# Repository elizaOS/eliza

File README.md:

# Eliza on Vibestack

This workspace specifies the replacement for `@elizaos/core` on Vibestack.
The specification covers requirements, Quint models, and the generated
contracts for a future VibeLang and Effect implementation.

Start with [the Grace and AlphaPhone contracts](spec/downstream/index.md),
[the core specification](spec/core/index.md),
[the agent procedure](AGENTS.md) and [the spec reference](SPEC.md).
The source baseline is Eliza commit
`72fed7e4069ecd35d61d886ab6eec5c02c137517`. The orphan `vibestack` branch
starts from elizaOS/eliza-vibestack commit
`71d7b30f404b91d7ec48741ac288d6c8d911f3e2`.

## Setup and verification

Use Node 26, pnpm 10.24.0 and Dafny 4.11.

```sh
pnpm install --frozen-lockfile
pnpm gen
pnpm check
pnpm verify
```

`pnpm check` generates the contracts, checks model traces and replay,
proves safety obligations, runs available journeys, and lists changes for
review. `pnpm accept` records the user's review. The imported application
in `apps/app` exercises the toolchain. Core implementation and npm
consumer acceptance are separate later work.

[The Vibestack toolchain guide](vibestack/README.md) explains Studio,
commands, examples and generated files. [Contributing](CONTRIBUTING.md)
describes the repository checks. The MIT license is in [LICENSE](LICENSE).

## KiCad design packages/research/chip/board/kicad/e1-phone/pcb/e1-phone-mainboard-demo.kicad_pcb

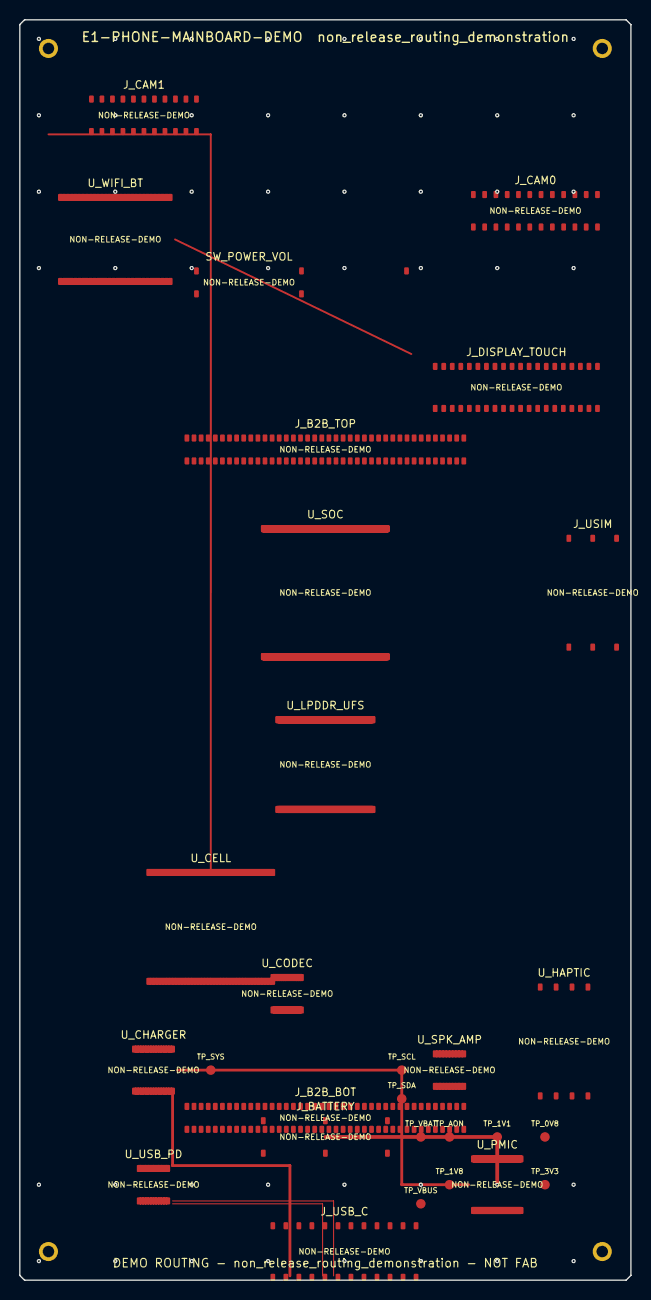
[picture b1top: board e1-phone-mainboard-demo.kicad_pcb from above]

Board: 10 copper layers, 64.0 x 132.0 mm, 29 parts (0 on the bottom side), 40 nets.

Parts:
J_B2B_BOT: DEMO; J_B2B_BOT
J_B2B_TOP: DEMO; J_B2B_TOP
J_BATTERY: DEMO; J_BATTERY
J_CAM0: DEMO; J_CAM0
J_CAM1: DEMO; J_CAM1
J_DISPLAY_TOUCH: DEMO; J_DISPLAY_TOUCH
J_USB_C: DEMO; J_USB_C
J_USIM: DEMO; J_USIM
SW_POWER_VOL: DEMO; SW_POWER_VOL
TP_0V8: +0V8; TP_0V8
TP_1V1: +1V1; TP_1V1
TP_1V8: +1V8; TP_1V8
TP_3V3: +3V3; TP_3V3
TP_AON: AON_1V8; TP_AON
TP_SCL: I2C0_SCL; TP_SCL
TP_SDA: I2C0_SDA; TP_SDA
TP_SYS: SYS; TP_SYS
TP_VBAT: VBAT; TP_VBAT
TP_VBUS: VBUS; TP_VBUS
U_CELL: DEMO; U_CELL
U_CHARGER: DEMO; U_CHARGER
U_CODEC: DEMO; U_CODEC
U_HAPTIC: DEMO; U_HAPTIC
U_LPDDR_UFS: DEMO; U_LPDDR_UFS
U_PMIC: DEMO; U_PMIC
U_SOC: DEMO; U_SOC
U_SPK_AMP: DEMO; U_SPK_AMP
U_USB_PD: DEMO; U_USB_PD
U_WIFI_BT: DEMO; U_WIFI_BT

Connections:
+0V8: TP_0V8.1, U_PMIC.7, U_PMIC.16, U_PMIC.25, U_PMIC.34, U_PMIC.43, U_PMIC.52, U_PMIC.61, U_SOC.1, U_SOC.9, U_SOC.17, U_SOC.25, U_SOC.33, U_SOC.41, U_SOC.49, U_SOC.57, U_SOC.65, U_SOC.73, U_SOC.81, U_SOC.89, U_SOC.97, U_SOC.105, U_SOC.113, U_SOC.121, U_SOC.129, U_SOC.137, U_SOC.145, U_SOC.153, U_SOC.161, U_SOC.169, U_SOC.177, U_SOC.185, U_SOC.193, U_SOC.201, U_SOC.209, U_SOC.217, U_SOC.225, U_SOC.233, U_SOC.241, U_SOC.249, U_SOC.257, U_SOC.265, U_SOC.273, U_SOC.281, U_SOC.289, U_SOC.297, U_SOC.305, U_SOC.313, U_SOC.321, U_SOC.329, U_SOC.337, U_SOC.345, U_SOC.353, U_SOC.361, U_SOC.369, U_SOC.377, U_SOC.385, U_SOC.393
+1V1: TP_1V1.1, U_LPDDR_UFS.1, U_LPDDR_UFS.4, U_LPDDR_UFS.7, U_LPDDR_UFS.10, U_LPDDR_UFS.13, U_LPDDR_UFS.16, U_LPDDR_UFS.19, U_LPDDR_UFS.22, U_LPDDR_UFS.25, U_LPDDR_UFS.28, U_LPDDR_UFS.31, U_LPDDR_UFS.34, U_LPDDR_UFS.37, U_LPDDR_UFS.40, U_LPDDR_UFS.43, U_LPDDR_UFS.46, U_LPDDR_UFS.49, U_LPDDR_UFS.52, U_LPDDR_UFS.55, U_LPDDR_UFS.58, U_LPDDR_UFS.61, U_LPDDR_UFS.64, U_LPDDR_UFS.67, U_LPDDR_UFS.70, U_LPDDR_UFS.73, U_LPDDR_UFS.76, U_LPDDR_UFS.79, U_LPDDR_UFS.82, U_LPDDR_UFS.85, U_LPDDR_UFS.88, U_LPDDR_UFS.91, U_LPDDR_UFS.94, U_LPDDR_UFS.97, U_LPDDR_UFS.100, U_LPDDR_UFS.103, U_LPDDR_UFS.106, U_LPDDR_UFS.109, U_LPDDR_UFS.112, U_LPDDR_UFS.115, U_LPDDR_UFS.118, U_LPDDR_UFS.121, U_LPDDR_UFS.124, U_LPDDR_UFS.127, U_LPDDR_UFS.130, U_LPDDR_UFS.133, U_LPDDR_UFS.136, U_LPDDR_UFS.139, U_LPDDR_UFS.142, U_LPDDR_UFS.145, U_LPDDR_UFS.148, U_LPDDR_UFS.151, U_LPDDR_UFS.154, U_LPDDR_UFS.157, U_LPDDR_UFS.160, U_LPDDR_UFS.163, U_LPDDR_UFS.166, U_LPDDR_UFS.169, U_LPDDR_UFS.172, U_LPDDR_UFS.175, U_LPDDR_UFS.178, U_LPDDR_UFS.181, U_LPDDR_UFS.184, U_LPDDR_UFS.187, U_LPDDR_UFS.190, U_LPDDR_UFS.193, U_LPDDR_UFS.196, U_LPDDR_UFS.199, U_PMIC.6, U_PMIC.15, U_PMIC.24, U_PMIC.33, U_PMIC.42, U_PMIC.51, U_PMIC.60, U_SOC.2, U_SOC.10, U_SOC.18, U_SOC.26, U_SOC.34, U_SOC.42, U_SOC.50, U_SOC.58, U_SOC.66, U_SOC.74, U_SOC.82, U_SOC.90, U_SOC.98, U_SOC.106, U_SOC.114, U_SOC.122, U_SOC.130, U_SOC.138, U_SOC.146, U_SOC.154, U_SOC.162, U_SOC.170, U_SOC.178, U_SOC.186, U_SOC.194, U_SOC.202, U_SOC.210, U_SOC.218, U_SOC.226, U_SOC.234, U_SOC.242, U_SOC.250, U_SOC.258, U_SOC.266, U_SOC.274, U_SOC.282, U_SOC.290, U_SOC.298, U_SOC.306, U_SOC.314, U_SOC.322, U_SOC.330, U_SOC.338, U_SOC.346, U_SOC.354, U_SOC.362, U_SOC.370, U_SOC.378, U_SOC.386, U_SOC.394
+1V8: J_B2B_BOT.4, J_B2B_BOT.10, J_B2B_BOT.16, J_B2B_BOT.22, J_B2B_BOT.28, J_B2B_BOT.34, J_B2B_BOT.40, J_B2B_BOT.46, J_B2B_BOT.52, J_B2B_BOT.58, J_B2B_BOT.64, J_B2B_BOT.70, J_B2B_BOT.76, J_B2B_TOP.4, J_B2B_TOP.10, J_B2B_TOP.16, J_B2B_TOP.22, J_B2B_TOP.28, J_B2B_TOP.34, J_B2B_TOP.40, J_B2B_TOP.46, J_B2B_TOP.52, J_B2B_TOP.58, J_B2B_TOP.64, J_B2B_TOP.70, J_B2B_TOP.76, J_CAM0.3, J_CAM0.11, J_CAM0.19, J_CAM1.3, J_CAM1.7, J_CAM1.11, J_CAM1.15, J_CAM1.19, J_DISPLAY_TOUCH.3, J_DISPLAY_TOUCH.11, J_DISPLAY_TOUCH.19, J_DISPLAY_TOUCH.27, J_DISPLAY_TOUCH.35, J_USIM.1, J_USIM.3, J_USIM.5, TP_1V8.1, U_CELL.2, U_CELL.10, U_CELL.18, U_CELL.26, U_CELL.34, U_CELL.42, U_CELL.50, U_CELL.58, U_CELL.66, U_CELL.74, U_LPDDR_UFS.2, U_LPDDR_UFS.5, U_LPDDR_UFS.8, U_LPDDR_UFS.11, U_LPDDR_UFS.14, U_LPDDR_UFS.17, U_LPDDR_UFS.20, U_LPDDR_UFS.23, U_LPDDR_UFS.26, U_LPDDR_UFS.29, U_LPDDR_UFS.32, U_LPDDR_UFS.35, U_LPDDR_UFS.38, U_LPDDR_UFS.41, U_LPDDR_UFS.44, U_LPDDR_UFS.47, U_LPDDR_UFS.50, U_LPDDR_UFS.53, U_LPDDR_UFS.56, U_LPDDR_UFS.59, U_LPDDR_UFS.62, U_LPDDR_UFS.65, U_LPDDR_UFS.68, U_LPDDR_UFS.71, U_LPDDR_UFS.74, U_LPDDR_UFS.77, U_LPDDR_UFS.80, U_LPDDR_UFS.83, U_LPDDR_UFS.86, U_LPDDR_UFS.89, U_LPDDR_UFS.92, U_LPDDR_UFS.95, U_LPDDR_UFS.98, U_LPDDR_UFS.101, U_LPDDR_UFS.104, U_LPDDR_UFS.107, U_LPDDR_UFS.110, U_LPDDR_UFS.113, U_LPDDR_UFS.116, U_LPDDR_UFS.119, U_LPDDR_UFS.122, U_LPDDR_UFS.125, U_LPDDR_UFS.128, U_LPDDR_UFS.131, U_LPDDR_UFS.134, U_LPDDR_UFS.137, U_LPDDR_UFS.140, U_LPDDR_UFS.143, U_LPDDR_UFS.146, U_LPDDR_UFS.149, U_LPDDR_UFS.152, U_LPDDR_UFS.155, U_LPDDR_UFS.158, U_LPDDR_UFS.161, U_LPDDR_UFS.164, U_LPDDR_UFS.167, U_LPDDR_UFS.170, U_LPDDR_UFS.173, U_LPDDR_UFS.176, U_LPDDR_UFS.179, U_LPDDR_UFS.182, U_LPDDR_UFS.185, U_LPDDR_UFS.188, U_LPDDR_UFS.191, U_LPDDR_UFS.194, U_LPDDR_UFS.197, U_LPDDR_UFS.200, U_PMIC.5, U_PMIC.14, U_PMIC.23, U_PMIC.32, U_PMIC.41, U_PMIC.50, U_PMIC.59, U_SOC.3, U_SOC.11, U_SOC.19, U_SOC.27, U_SOC.35, U_SOC.43, U_SOC.51, U_SOC.59, U_SOC.67, U_SOC.75, U_SOC.83, U_SOC.91, U_SOC.99, U_SOC.107, U_SOC.115, U_SOC.123, U_SOC.131, U_SOC.139, U_SOC.147, U_SOC.155, U_SOC.163, U_SOC.171, U_SOC.179, U_SOC.187, U_SOC.195, U_SOC.203, U_SOC.211, U_SOC.219, U_SOC.227, U_SOC.235, U_SOC.243, U_SOC.251, U_SOC.259, U_SOC.267, U_SOC.275, U_SOC.283, U_SOC.291, U_SOC.299, U_SOC.307, U_SOC.315, U_SOC.323, U_SOC.331, U_SOC.339, U_SOC.347, U_SOC.355, U_SOC.363, U_SOC.371, U_SOC.379, U_SOC.387, U_SOC.395, U_WIFI_BT.2, U_WIFI_BT.12, U_WIFI_BT.22, U_WIFI_BT.32, U_WIFI_BT.42, U_WIFI_BT.52
+3V3: TP_3V3.1, U_PMIC.4, U_PMIC.13, U_PMIC.22, U_PMIC.31, U_PMIC.40, U_PMIC.49, U_PMIC.58, U_USB_PD.4, U_USB_PD.11, U_USB_PD.18
AON_1V8: J_B2B_BOT.3, J_B2B_BOT.9, J_B2B_BOT.15, J_B2B_BOT.21, J_B2B_BOT.27, J_B2B_BOT.33, J_B2B_BOT.39, J_B2B_BOT.45, J_B2B_BOT.51, J_B2B_BOT.57, J_B2B_BOT.63, J_B2B_BOT.69, J_B2B_BOT.75, J_B2B_TOP.3, J_B2B_TOP.9, J_B2B_TOP.15, J_B2B_TOP.21, J_B2B_TOP.27, J_B2B_TOP.33, J_B2B_TOP.39, J_B2B_TOP.45, J_B2B_TOP.51, J_B2B_TOP.57, J_B2B_TOP.63, J_B2B_TOP.69, J_B2B_TOP.75, SW_POWER_VOL.4, TP_AON.1, U_CELL.3, U_CELL.11, U_CELL.19, U_CELL.27, U_CELL.35, U_CELL.43, U_CELL.51, U_CELL.59, U_CELL.67, U_CELL.75, U_CODEC.2, U_CODEC.7, U_CODEC.12, U_CODEC.17, U_CODEC.22, U_CODEC.27, U_CODEC.32, U_PMIC.8, U_PMIC.17, U_PMIC.26, U_PMIC.35, U_PMIC.44, U_PMIC.53, U_PMIC.62
BT_EN: U_WIFI_BT.5, U_WIFI_BT.15, U_WIFI_BT.25, U_WIFI_BT.35, U_WIFI_BT.45, U_WIFI_BT.55
BT_UART_RX: U_WIFI_BT.8, U_WIFI_BT.18, U_WIFI_BT.28, U_WIFI_BT.38, U_WIFI_BT.48, U_WIFI_BT.58
BT_UART_TX: U_WIFI_BT.7, U_WIFI_BT.17, U_WIFI_BT.27, U_WIFI_BT.37, U_WIFI_BT.47, U_WIFI_BT.57
CAM0_CSI_CLK_N: J_CAM0.6, J_CAM0.14, J_CAM0.22
CAM0_CSI_CLK_P: J_CAM0.5, J_CAM0.13, J_CAM0.21
CAM_AVDD_2V8: J_CAM0.1, J_CAM0.9, J_CAM0.17, J_CAM1.1, J_CAM1.5, J_CAM1.9, J_CAM1.13, J_CAM1.17, J_CAM1.21
CAM_DVDD_1V2: J_CAM0.2, J_CAM0.10, J_CAM0.18, J_CAM1.2, J_CAM1.6, J_CAM1.10, J_CAM1.14, J_CAM1.18, J_CAM1.22
CELL_GNSS_RF: U_CELL.8, U_CELL.16, U_CELL.24, U_CELL.32, U_CELL.40, U_CELL.48, U_CELL.56, U_CELL.64, U_CELL.72, U_CELL.80
CELL_RESET_N: U_CELL.5, U_CELL.13, U_CELL.21, U_CELL.29, U_CELL.37, U_CELL.45, U_CELL.53, U_CELL.61, U_CELL.69, U_CELL.77
CELL_RF_DIV: U_CELL.7, U_CELL.15, U_CELL.23, U_CELL.31, U_CELL.39, U_CELL.47, U_CELL.55, U_CELL.63, U_CELL.71, U_CELL.79
CELL_RF_MAIN: U_CELL.6, U_CELL.14, U_CELL.22, U_CELL.30, U_CELL.38, U_CELL.46, U_CELL.54, U_CELL.62, U_CELL.70, U_CELL.78
DISP_AVDD_5V5: J_DISPLAY_TOUCH.1, J_DISPLAY_TOUCH.9, J_DISPLAY_TOUCH.17, J_DISPLAY_TOUCH.25, J_DISPLAY_TOUCH.33
DISP_AVEE_N5V5: J_DISPLAY_TOUCH.2, J_DISPLAY_TOUCH.10, J_DISPLAY_TOUCH.18, J_DISPLAY_TOUCH.26, J_DISPLAY_TOUCH.34
DSI_CLK_N: J_DISPLAY_TOUCH.6, J_DISPLAY_TOUCH.14, J_DISPLAY_TOUCH.22, J_DISPLAY_TOUCH.30, J_DISPLAY_TOUCH.38, U_SOC.8, U_SOC.16, U_SOC.24, U_SOC.32, U_SOC.40, U_SOC.48, U_SOC.56, U_SOC.64, U_SOC.72, U_SOC.80, U_SOC.88, U_SOC.96, U_SOC.104, U_SOC.112, U_SOC.120, U_SOC.128, U_SOC.136, U_SOC.144, U_SOC.152, U_SOC.160, U_SOC.168, U_SOC.176, U_SOC.184, U_SOC.192, U_SOC.200, U_SOC.208, U_SOC.216, U_SOC.224, U_SOC.232, U_SOC.240, U_SOC.248, U_SOC.256, U_SOC.264, U_SOC.272, U_SOC.280, U_SOC.288, U_SOC.296, U_SOC.304, U_SOC.312, U_SOC.320, U_SOC.328, U_SOC.336, U_SOC.344, U_SOC.352, U_SOC.360, U_SOC.368, U_SOC.376, U_SOC.384, U_SOC.392, U_SOC.400
DSI_CLK_P: J_DISPLAY_TOUCH.5, J_DISPLAY_TOUCH.13, J_DISPLAY_TOUCH.21, J_DISPLAY_TOUCH.29, J_DISPLAY_TOUCH.37, U_SOC.7, U_SOC.15, U_SOC.23, U_SOC.31, U_SOC.39, U_SOC.47, U_SOC.55, U_SOC.63, U_SOC.71, U_SOC.79, U_SOC.87, U_SOC.95, U_SOC.103, U_SOC.111, U_SOC.119, U_SOC.127, U_SOC.135, U_SOC.143, U_SOC.151, U_SOC.159, U_SOC.167, U_SOC.175, U_SOC.183, U_SOC.191, U_SOC.199, U_SOC.207, U_SOC.215, U_SOC.223, U_SOC.231, U_SOC.239, U_SOC.247, U_SOC.255, U_SOC.263, U_SOC.271, U_SOC.279, U_SOC.287, U_SOC.295, U_SOC.303, U_SOC.311, U_SOC.319, U_SOC.327, U_SOC.335, U_SOC.343, U_SOC.351, U_SOC.359, U_SOC.367, U_SOC.375, U_SOC.383, U_SOC.391, U_SOC.399
DSI_D0_N: J_DISPLAY_TOUCH.8, J_DISPLAY_TOUCH.16, J_DISPLAY_TOUCH.24, J_DISPLAY_TOUCH.32, J_DISPLAY_TOUCH.40
DSI_D0_P: J_DISPLAY_TOUCH.7, J_DISPLAY_TOUCH.15, J_DISPLAY_TOUCH.23, J_DISPLAY_TOUCH.31, J_DISPLAY_TOUCH.39
GND: J_B2B_BOT.6, J_B2B_BOT.12, J_B2B_BOT.18, J_B2B_BOT.24, J_B2B_BOT.30, J_B2B_BOT.36, J_B2B_BOT.42, J_B2B_BOT.48, J_B2B_BOT.54, J_B2B_BOT.60, J_B2B_BOT.66, J_B2B_BOT.72, J_B2B_BOT.78, J_B2B_TOP.6, J_B2B_TOP.12, J_B2B_TOP.18, J_B2B_TOP.24, J_B2B_TOP.30, J_B2B_TOP.36, J_B2B_TOP.42, J_B2B_TOP.48, J_B2B_TOP.54, J_B2B_TOP.60, J_B2B_TOP.66, J_B2B_TOP.72, J_B2B_TOP.78, J_BATTERY.2, J_BATTERY.4, J_BATTERY.6, J_CAM0.4, J_CAM0.12, J_CAM0.20, J_CAM1.4, J_CAM1.8, J_CAM1.12, J_CAM1.16, J_CAM1.20, J_DISPLAY_TOUCH.4, J_DISPLAY_TOUCH.12, J_DISPLAY_TOUCH.20, J_DISPLAY_TOUCH.28, J_DISPLAY_TOUCH.36, J_USB_C.7, J_USB_C.15, J_USB_C.23, J_USIM.2, J_USIM.4, J_USIM.6, SW_POWER_VOL.5, U_CELL.4, U_CELL.12, U_CELL.20, U_CELL.28, U_CELL.36, U_CELL.44, U_CELL.52, U_CELL.60, U_CELL.68, U_CELL.76, U_CHARGER.4, U_CHARGER.10, U_CHARGER.16, U_CHARGER.22, U_CHARGER.28, U_CODEC.3, U_CODEC.8, U_CODEC.13, U_CODEC.18, U_CODEC.23, U_CODEC.28, U_HAPTIC.2, U_HAPTIC.4, U_HAPTIC.6, U_HAPTIC.8, U_LPDDR_UFS.3, U_LPDDR_UFS.6, U_LPDDR_UFS.9, U_LPDDR_UFS.12, U_LPDDR_UFS.15, U_LPDDR_UFS.18, U_LPDDR_UFS.21, U_LPDDR_UFS.24, U_LPDDR_UFS.27, U_LPDDR_UFS.30, U_LPDDR_UFS.33, U_LPDDR_UFS.36, U_LPDDR_UFS.39, U_LPDDR_UFS.42, U_LPDDR_UFS.45, U_LPDDR_UFS.48, U_LPDDR_UFS.51, U_LPDDR_UFS.54, U_LPDDR_UFS.57, U_LPDDR_UFS.60, U_LPDDR_UFS.63, U_LPDDR_UFS.66, U_LPDDR_UFS.69, U_LPDDR_UFS.72, U_LPDDR_UFS.75, U_LPDDR_UFS.78, U_LPDDR_UFS.81, U_LPDDR_UFS.84, U_LPDDR_UFS.87, U_LPDDR_UFS.90, U_LPDDR_UFS.93, U_LPDDR_UFS.96, U_LPDDR_UFS.99, U_LPDDR_UFS.102, U_LPDDR_UFS.105, U_LPDDR_UFS.108, U_LPDDR_UFS.111, U_LPDDR_UFS.114, U_LPDDR_UFS.117, U_LPDDR_UFS.120, U_LPDDR_UFS.123, U_LPDDR_UFS.126, U_LPDDR_UFS.129, U_LPDDR_UFS.132, U_LPDDR_UFS.135, U_LPDDR_UFS.138, U_LPDDR_UFS.141, U_LPDDR_UFS.144, U_LPDDR_UFS.147, U_LPDDR_UFS.150, U_LPDDR_UFS.153, U_LPDDR_UFS.156, U_LPDDR_UFS.159, U_LPDDR_UFS.162, U_LPDDR_UFS.165, U_LPDDR_UFS.168, U_LPDDR_UFS.171, U_LPDDR_UFS.174, U_LPDDR_UFS.177, U_LPDDR_UFS.180, U_LPDDR_UFS.183, U_LPDDR_UFS.186, U_LPDDR_UFS.189, U_LPDDR_UFS.192, U_LPDDR_UFS.195, U_LPDDR_UFS.198, U_PMIC.3, U_PMIC.12, U_PMIC.21, U_PMIC.30, U_PMIC.39, U_PMIC.48, U_PMIC.57, U_SOC.4, U_SOC.12, U_SOC.20, U_SOC.28, U_SOC.36, U_SOC.44, U_SOC.52, U_SOC.60, U_SOC.68, U_SOC.76, U_SOC.84, U_SOC.92, U_SOC.100, U_SOC.108, U_SOC.116, U_SOC.124, U_SOC.132, U_SOC.140, U_SOC.148, U_SOC.156, U_SOC.164, U_SOC.172, U_SOC.180, U_SOC.188, U_SOC.196, U_SOC.204, U_SOC.212, U_SOC.220, U_SOC.228, U_SOC.236, U_SOC.244, U_SOC.252, U_SOC.260, U_SOC.268, U_SOC.276, U_SOC.284, U_SOC.292, U_SOC.300, U_SOC.308, U_SOC.316, U_SOC.324, U_SOC.332, U_SOC.340, U_SOC.348, U_SOC.356, U_SOC.364, U_SOC.372, U_SOC.380, U_SOC.388, U_SOC.396, U_SPK_AMP.2, U_SPK_AMP.4, U_SPK_AMP.6, U_SPK_AMP.8, U_SPK_AMP.10, U_SPK_AMP.12, U_SPK_AMP.14, U_SPK_AMP.16, U_SPK_AMP.18, U_SPK_AMP.20, U_USB_PD.5, U_USB_PD.12, U_USB_PD.19, U_WIFI_BT.3, U_WIFI_BT.13, U_WIFI_BT.23, U_WIFI_BT.33, U_WIFI_BT.43, U_WIFI_BT.53
I2C0_SCL: J_CAM0.7, J_CAM0.15, J_CAM0.23, TP_SCL.1, U_CHARGER.5, U_CHARGER.11, U_CHARGER.17, U_CHARGER.23, U_CHARGER.29, U_CODEC.4, U_CODEC.9, U_CODEC.14, U_CODEC.19, U_CODEC.24, U_CODEC.29, U_USB_PD.6, U_USB_PD.13, U_USB_PD.20
I2C0_SDA: J_CAM0.8, J_CAM0.16, J_CAM0.24, TP_SDA.1, U_CHARGER.6, U_CHARGER.12, U_CHARGER.18, U_CHARGER.24, U_CHARGER.30, U_CODEC.5, U_CODEC.10, U_CODEC.15, U_CODEC.20, U_CODEC.25, U_CODEC.30, U_USB_PD.7, U_USB_PD.14, U_USB_PD.21
RF_VBAT: J_B2B_BOT.5, J_B2B_BOT.11, J_B2B_BOT.17, J_B2B_BOT.23, J_B2B_BOT.29, J_B2B_BOT.35, J_B2B_BOT.41, J_B2B_BOT.47, J_B2B_BOT.53, J_B2B_BOT.59, J_B2B_BOT.65, J_B2B_BOT.71, J_B2B_BOT.77, J_B2B_TOP.5, J_B2B_TOP.11, J_B2B_TOP.17, J_B2B_TOP.23, J_B2B_TOP.29, J_B2B_TOP.35, J_B2B_TOP.41, J_B2B_TOP.47, J_B2B_TOP.53, J_B2B_TOP.59, J_B2B_TOP.65, J_B2B_TOP.71, J_B2B_TOP.77, U_CELL.1, U_CELL.9, U_CELL.17, U_CELL.25, U_CELL.33, U_CELL.41, U_CELL.49, U_CELL.57, U_CELL.65, U_CELL.73, U_PMIC.9, U_PMIC.18, U_PMIC.27, U_PMIC.36, U_PMIC.45, U_PMIC.54, U_PMIC.63, U_WIFI_BT.1, U_WIFI_BT.11, U_WIFI_BT.21, U_WIFI_BT.31, U_WIFI_BT.41, U_WIFI_BT.51
SDIO_CLK: U_WIFI_BT.9, U_WIFI_BT.19, U_WIFI_BT.29, U_WIFI_BT.39, U_WIFI_BT.49, U_WIFI_BT.59
SDIO_CMD: U_WIFI_BT.10, U_WIFI_BT.20, U_WIFI_BT.30, U_WIFI_BT.40, U_WIFI_BT.50, U_WIFI_BT.60
SHIELD_GND: J_USB_C.6, J_USB_C.14, J_USB_C.22
SYS: J_B2B_BOT.2, J_B2B_BOT.8, J_B2B_BOT.14, J_B2B_BOT.20, J_B2B_BOT.26, J_B2B_BOT.32, J_B2B_BOT.38, J_B2B_BOT.44, J_B2B_BOT.50, J_B2B_BOT.56, J_B2B_BOT.62, J_B2B_BOT.68, J_B2B_BOT.74, J_B2B_BOT.80, J_B2B_TOP.2, J_B2B_TOP.8, J_B2B_TOP.14, J_B2B_TOP.20, J_B2B_TOP.26, J_B2B_TOP.32, J_B2B_TOP.38, J_B2B_TOP.44, J_B2B_TOP.50, J_B2B_TOP.56, J_B2B_TOP.62, J_B2B_TOP.68, J_B2B_TOP.74, J_B2B_TOP.80, TP_SYS.1, U_CHARGER.2, U_CHARGER.8, U_CHARGER.14, U_CHARGER.20, U_CHARGER.26, U_CHARGER.32, U_PMIC.1, U_PMIC.10, U_PMIC.19, U_PMIC.28, U_PMIC.37, U_PMIC.46, U_PMIC.55, U_PMIC.64
USB_CC1: J_USB_C.4, J_USB_C.12, J_USB_C.20, U_USB_PD.2, U_USB_PD.9, U_USB_PD.16, U_USB_PD.23
USB_CC2: J_USB_C.5, J_USB_C.13, J_USB_C.21, U_USB_PD.3, U_USB_PD.10, U_USB_PD.17, U_USB_PD.24
USB_DN: J_USB_C.3, J_USB_C.11, J_USB_C.19, U_SOC.6, U_SOC.14, U_SOC.22, U_SOC.30, U_SOC.38, U_SOC.46, U_SOC.54, U_SOC.62, U_SOC.70, U_SOC.78, U_SOC.86, U_SOC.94, U_SOC.102, U_SOC.110, U_SOC.118, U_SOC.126, U_SOC.134, U_SOC.142, U_SOC.150, U_SOC.158, U_SOC.166, U_SOC.174, U_SOC.182, U_SOC.190, U_SOC.198, U_SOC.206, U_SOC.214, U_SOC.222, U_SOC.230, U_SOC.238, U_SOC.246, U_SOC.254, U_SOC.262, U_SOC.270, U_SOC.278, U_SOC.286, U_SOC.294, U_SOC.302, U_SOC.310, U_SOC.318, U_SOC.326, U_SOC.334, U_SOC.342, U_SOC.350, U_SOC.358, U_SOC.366, U_SOC.374, U_SOC.382, U_SOC.390, U_SOC.398
USB_DP: J_USB_C.2, J_USB_C.10, J_USB_C.18, U_SOC.5, U_SOC.13, U_SOC.21, U_SOC.29, U_SOC.37, U_SOC.45, U_SOC.53, U_SOC.61, U_SOC.69, U_SOC.77, U_SOC.85, U_SOC.93, U_SOC.101, U_SOC.109, U_SOC.117, U_SOC.125, U_SOC.133, U_SOC.141, U_SOC.149, U_SOC.157, U_SOC.165, U_SOC.173, U_SOC.181, U_SOC.189, U_SOC.197, U_SOC.205, U_SOC.213, U_SOC.221, U_SOC.229, U_SOC.237, U_SOC.245, U_SOC.253, U_SOC.261, U_SOC.269, U_SOC.277, U_SOC.285, U_SOC.293, U_SOC.301, U_SOC.309, U_SOC.317, U_SOC.325, U_SOC.333, U_SOC.341, U_SOC.349, U_SOC.357, U_SOC.365, U_SOC.373, U_SOC.381, U_SOC.389, U_SOC.397
VBAT: J_B2B_BOT.1, J_B2B_BOT.7, J_B2B_BOT.13, J_B2B_BOT.19, J_B2B_BOT.25, J_B2B_BOT.31, J_B2B_BOT.37, J_B2B_BOT.43, J_B2B_BOT.49, J_B2B_BOT.55, J_B2B_BOT.61, J_B2B_BOT.67, J_B2B_BOT.73, J_B2B_BOT.79, J_B2B_TOP.1, J_B2B_TOP.7, J_B2B_TOP.13, J_B2B_TOP.19, J_B2B_TOP.25, J_B2B_TOP.31, J_B2B_TOP.37, J_B2B_TOP.43, J_B2B_TOP.49, J_B2B_TOP.55, J_B2B_TOP.61, J_B2B_TOP.67, J_B2B_TOP.73, J_B2B_TOP.79, J_BATTERY.1, J_BATTERY.3, J_BATTERY.5, TP_VBAT.1, U_CHARGER.3, U_CHARGER.9, U_CHARGER.15, U_CHARGER.21, U_CHARGER.27, U_HAPTIC.1, U_HAPTIC.3, U_HAPTIC.5, U_HAPTIC.7, U_PMIC.2, U_PMIC.11, U_PMIC.20, U_PMIC.29, U_PMIC.38, U_PMIC.47, U_PMIC.56
VBUS: J_USB_C.1, J_USB_C.8, J_USB_C.9, J_USB_C.16, J_USB_C.17, J_USB_C.24, TP_VBUS.1, U_CHARGER.1, U_CHARGER.7, U_CHARGER.13, U_CHARGER.19, U_CHARGER.25, U_CHARGER.31, U_USB_PD.1, U_USB_PD.8, U_USB_PD.15, U_USB_PD.22
VDD_AMP_3V3: U_SPK_AMP.1, U_SPK_AMP.3, U_SPK_AMP.5, U_SPK_AMP.7, U_SPK_AMP.9, U_SPK_AMP.11, U_SPK_AMP.13, U_SPK_AMP.15, U_SPK_AMP.17, U_SPK_AMP.19
VDD_AUDIO_3V3: U_CODEC.1, U_CODEC.6, U_CODEC.11, U_CODEC.16, U_CODEC.21, U_CODEC.26, U_CODEC.31
WIFI_BT_RF: U_WIFI_BT.6, U_WIFI_BT.16, U_WIFI_BT.26, U_WIFI_BT.36, U_WIFI_BT.46, U_WIFI_BT.56
WIFI_EN: U_WIFI_BT.4, U_WIFI_BT.14, U_WIFI_BT.24, U_WIFI_BT.34, U_WIFI_BT.44, U_WIFI_BT.54

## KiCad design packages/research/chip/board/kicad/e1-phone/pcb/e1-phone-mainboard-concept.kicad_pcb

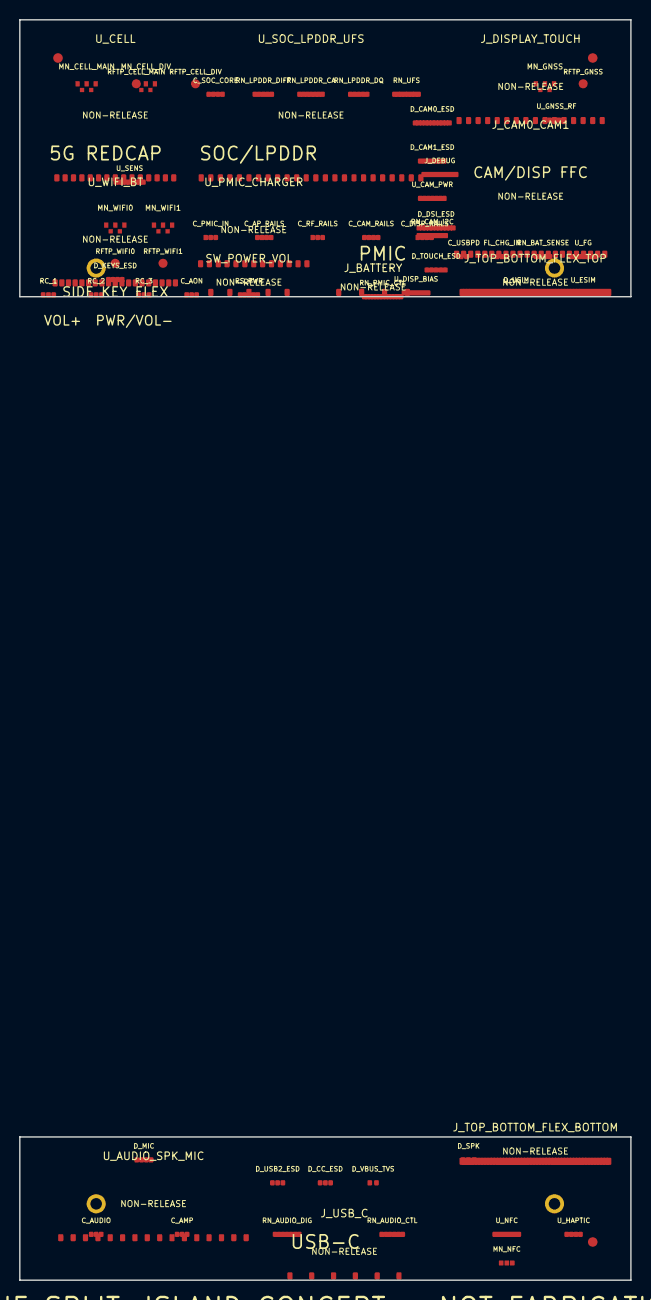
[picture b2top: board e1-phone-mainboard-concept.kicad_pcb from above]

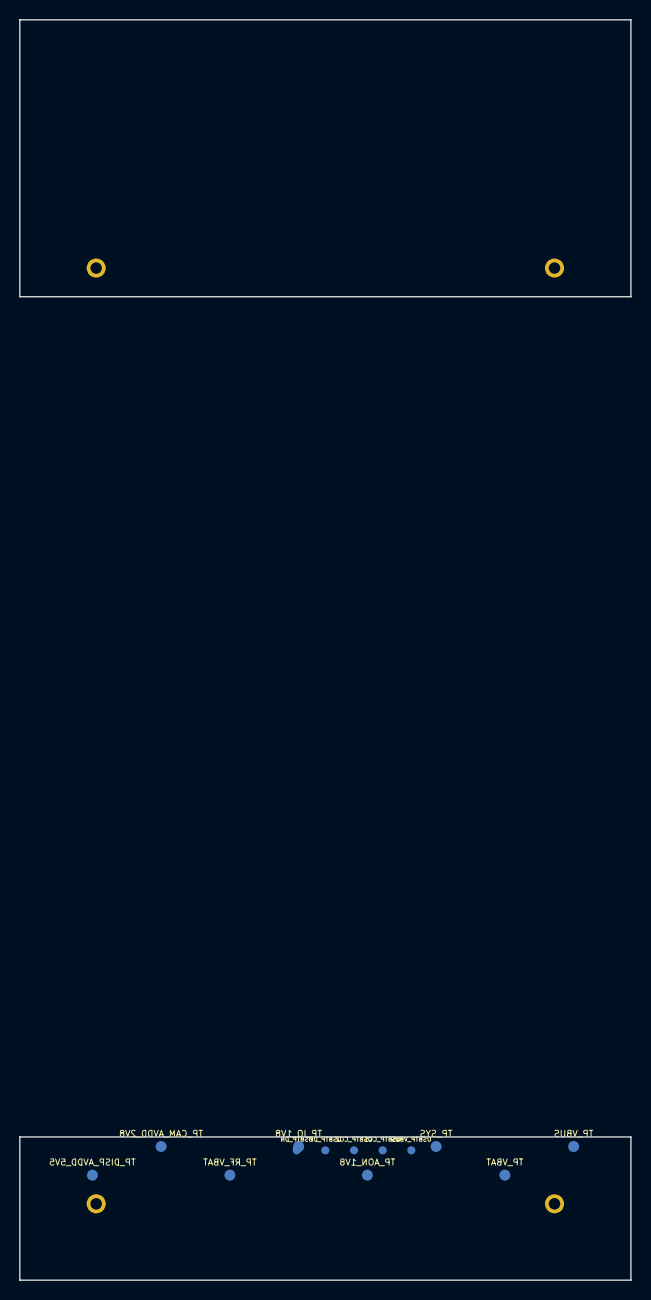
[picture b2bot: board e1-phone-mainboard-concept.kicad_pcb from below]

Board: 10 copper layers, 64.0 x 132.0 mm, 87 parts (13 on the bottom side), 103 nets, no tracks yet.

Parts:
C_AMP: SMART_AMP_RAIL_DECOUPLING; AUDIO_AMP_RAIL_DECOUPLING
C_AON: AON_BUTTON_WAKE_DECOUPLING; POWER_AON_BUTTON_WAKE_DECOUPLING
C_AP_RAILS: AP_CORE_IO_DECOUPLING; POWER_AP_RAIL_DECOUPLING
C_AUDIO: AUDIO_CODEC_RAIL_DECOUPLING
C_CAM_RAILS: CAMERA_AVDD_DVDD_DECOUPLING; POWER_CAMERA_RAIL_DECOUPLING
C_DISP_RAILS: DISPLAY_BIAS_DECOUPLING; POWER_DISPLAY_RAIL_DECOUPLING
C_PMIC_IN: PMIC_SYS_VBAT_INPUT_DECOUPLING; POWER_PMIC_INPUT_DECOUPLING
C_RF_RAILS: RF_VBAT_IO_DECOUPLING; POWER_RF_RAIL_DECOUPLING
C_SOC_CORE: SOC_CORE_IO_DECOUPLING; COMPUTE_SOC_LOCAL_DECOUPLING
C_USBPD: USBPD_VIN_DECOUPLING; POWER_USBPD_LOCAL_RAIL
D_CAM0_ESD: CAM0_CSI_ESD_ARRAY; CAMERA_CSI0_ESD
D_CAM1_ESD: CAM1_CSI_ESD_ARRAY; CAMERA_CSI1_ESD
D_CC_ESD: CC_ESD_ARRAY; USB_PROTECT_CC_ESD
D_DSI_ESD: DSI_4LANE_ESD_ARRAY; DISPLAY_DSI_ESD
D_KEYS_ESD: SIDE_KEY_ESD_ARRAY; SIDE_KEY_ESD
D_MIC: PDM_MIC_ESD_BIAS_PLACEHOLDER; AUDIO_MIC_BIAS_ESD
D_SPK: SPEAKER_OUTPUT_PROTECT; AUDIO_SPK_OUTPUT_PROTECT
D_TOUCH_ESD: TOUCH_CONTROL_ESD; DISPLAY_TOUCH_CTRL_ESD
D_USB2_ESD: USB2_ESD_ARRAY; USB_PROTECT_USB2_ESD
D_USIM: USIM_ESD_LEVEL_SHIFT_PLACEHOLDER; PHONE_IDENTITY_USIM_ESD_LEVELSHIFT
D_VBUS_TVS: VBUS_TVS; USB_PROTECT_VBUS_TVS
FID_BR: FIDUCIAL; FID_BR
FID_TL: FIDUCIAL; FID_TL
FID_TR: FIDUCIAL; FID_TR
FL_CHG_IN: VBUS_CHARGER_INPUT_FILTER; POWER_CHARGER_INPUT_FILTER
J_BATTERY: battery_pack_power_thermistor_id; J_BATTERY
J_CAM0_CAM1: rear_and_front_mipi_csi_camera_fpc_connector_esca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; J_CAM0_CAM1
J_DEBUG: JTAG_BOOT_STRAP_TEST_ACCESS; COMPUTE_DEBUG_BOOT_STRAPS
J_DISPLAY_TOUCH: 5p5_in_fhd_mipi_display_touch_fpc_connector_escape; J_DISPLAY_TOUCH
J_TOP_BOTTOM_FLEX_BOTTOM: bottom_mate_for_split_board_interconnect; J_TOP_BOTTOM_FLEX_BOTTOM
J_TOP_BOTTOM_FLEX_TOP: top_mate_for_split_board_interconnect; J_TOP_BOTTOM_FLEX_TOP
J_USB_C: charging_data_debug_single_usb_c_port; J_USB_C
MH_BL: MOUNT; MH_BL
MH_BR: MOUNT; MH_BR
MH_TL: MOUNT; MH_TL
MH_TR: MOUNT; MH_TR
MN_CELL_DIV: CELL_RF_DIV_PI_MATCH; RF_MATCH_CELL_RF_DIV
MN_CELL_MAIN: CELL_RF_MAIN_PI_MATCH; RF_MATCH_CELL_RF_MAIN
MN_GNSS: CELL_GNSS_RF_PI_MATCH; RF_MATCH_CELL_GNSS_RF
MN_NFC: NFC_LOOP_MATCH_PLACEHOLDER; PHONE_IDENTITY_NFC_LOOP_MATCH
MN_WIFI0: WIFI_BT_RF0_PI_MATCH; RF_MATCH_WIFI_BT_RF0
MN_WIFI1: WIFI_BT_RF1_PI_MATCH; RF_MATCH_WIFI_BT_RF1
RC_1: PWR_KEY_N_RC_DEBOUNCE; SIDE_KEY_COND_PWR_KEY_N
RC_2: VOL_UP_N_RC_DEBOUNCE; SIDE_KEY_COND_VOL_UP_N
RC_3: VOL_DOWN_N_RC_DEBOUNCE; SIDE_KEY_COND_VOL_DOWN_N
RFTP_CELL_DIV: CELL_RF_DIV; RF_TP_CELL_RF_DIV
RFTP_CELL_MAIN: CELL_RF_MAIN; RF_TP_CELL_RF_MAIN
RFTP_GNSS: CELL_GNSS_RF; RF_TP_CELL_GNSS_RF
RFTP_WIFI0: WIFI_BT_RF0; RF_TP_WIFI_BT_RF0
RFTP_WIFI1: WIFI_BT_RF1; RF_TP_WIFI_BT_RF1
RN_AUDIO_CTL: AUDIO_I2C_IRQ_PULLUPS
RN_AUDIO_DIG: I2S_PDM_DAMPING_PLACEHOLDER; AUDIO_I2S_PDM_DAMPING
RN_BAT_SENSE: BATTERY_NTC_ID_SENSE; POWER_CHARGER_BATTERY_SENSE
RN_CAM_I2C: CAMERA_I2C_AF_PULLUPS
RN_LPDDR_CA: LPDDR_CA_DAMPING_PLACEHOLDER; COMPUTE_LPDDR_CA_DAMPING
RN_LPDDR_DIFF: LPDDR_CK_DQS_TERM_PLACEHOLDER; COMPUTE_LPDDR_CK_DQS_TERM
RN_LPDDR_DQ: LPDDR_DQ_ESCAPE_PLACEHOLDER; COMPUTE_LPDDR_DQ_ESCAPE
RN_PMIC_CTL: PMIC_CHARGER_PD_I2C_IRQ_PULLUPS; POWER_PMIC_CONTROL_PULLUPS
RN_UFS: UFS_MPHY_ESD_TERM_PLACEHOLDER; COMPUTE_UFS_MPHY_ESD_TERM
RS_PWR: VBUS_VBAT_SYS_CURRENT_SENSE; POWER_HIGH_CURRENT_SHUNT_PLACEHOLDERS
SW_POWER_VOL: power_volume_side_key_flex_connector; SW_POWER_VOL
TP_AON_1V8: AON_1V8; TP_AON_1V8
TP_CAM_AVDD_2V8: CAM_AVDD_2V8; TP_CAM_AVDD_2V8
TP_DISP_AVDD_5V5: DISP_AVDD_5V5; TP_DISP_AVDD_5V5
TP_IO_1V8: IO_1V8; TP_IO_1V8
TP_RF_VBAT: RF_VBAT; TP_RF_VBAT
TP_SYS: SYS; TP_SYS
TP_VBAT: VBAT; TP_VBAT
TP_VBUS: VBUS; TP_VBUS
USBTP_CC1: USB_CC1; USB_TP_CC1
USBTP_CC2: USB_CC2; USB_TP_CC2
USBTP_DN: USB_DN; USB_TP_DN
USBTP_DP: USB_DP; USB_TP_DP
USBTP_VBUS: VBUS; USB_TP_VBUS
U_AUDIO_SPK_MIC: bottom_left_audio_codec_speaker_microphone_haptic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; U_AUDIO_SPK_MIC
U_CAM_PWR: CAMERA_POWER_SEQUENCE_PLACEHOLDER; CAMERA_POWER_SEQUENCE
U_CELL: cellular_5g_redcap_module; U_CELL
U_DISP_BIAS: DISPLAY_BIAS_BACKLIGHT_PLACEHOLDER; DISPLAY_BIAS_BACKLIGHT
U_ESIM: ESIM_MODULE_PLACEHOLDER; PHONE_IDENTITY_ESIM_PLACEHOLDER
U_FG: FUEL_GAUGE_PLACEHOLDER; POWER_FUEL_GAUGE_PLACEHOLDER
U_GNSS_RF: GNSS_LNA_SAW_PLACEHOLDER; PHONE_IDENTITY_GNSS_LNA_SAW
U_HAPTIC: HAPTIC_DRIVER_PLACEHOLDER; HAPTIC_DRIVER_OUTPUT
U_NFC: NFC_CONTROLLER_PLACEHOLDER; PHONE_IDENTITY_NFC_CONTROLLER
U_PMIC_CHARGER: pmic_charger_power_path; U_PMIC_CHARGER
U_SENS: IMU_ALS_PROX_BARO_PLACEHOLDER; PHONE_IDENTITY_SENSOR_HUB
U_SOC_LPDDR_UFS: compute_memory_storage; U_SOC_LPDDR_UFS
U_WIFI_BT: wifi_6e_bluetooth_module; U_WIFI_BT

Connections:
AMP_INT: J_TOP_BOTTOM_FLEX_BOTTOM.21, J_TOP_BOTTOM_FLEX_TOP.21, RN_AUDIO_CTL.4, U_AUDIO_SPK_MIC.10
AON_1V8: C_AON.1, J_TOP_BOTTOM_FLEX_BOTTOM.8, J_TOP_BOTTOM_FLEX_TOP.8, RC_1.2, RC_2.2, RC_3.2, RN_PMIC_CTL.12, SW_POWER_VOL.4, TP_AON_1V8.1, U_AUDIO_SPK_MIC.14, U_PMIC_CHARGER.4, U_SENS.7
AP_0V8: C_AP_RAILS.1, C_SOC_CORE.1, U_PMIC_CHARGER.5, U_SOC_LPDDR_UFS.15
AP_1V1: C_AP_RAILS.2, C_SOC_CORE.2, U_PMIC_CHARGER.6, U_SOC_LPDDR_UFS.16
AUDIO_I2C_SCL: J_TOP_BOTTOM_FLEX_BOTTOM.18, J_TOP_BOTTOM_FLEX_TOP.18, RN_AUDIO_CTL.1, U_AUDIO_SPK_MIC.7
AUDIO_I2C_SDA: J_TOP_BOTTOM_FLEX_BOTTOM.19, J_TOP_BOTTOM_FLEX_TOP.19, RN_AUDIO_CTL.2, U_AUDIO_SPK_MIC.8
BAT_ID: J_BATTERY.4, RN_BAT_SENSE.3, U_FG.6
BAT_NTC: J_BATTERY.3, RN_BAT_SENSE.2, U_FG.5
CAM0_CSI_CLK_N: D_CAM0_ESD.2, J_CAM0_CAM1.1
CAM0_CSI_CLK_P: D_CAM0_ESD.1, J_CAM0_CAM1.2
CAM0_CSI_D0_N: D_CAM0_ESD.4, J_CAM0_CAM1.3
CAM0_CSI_D0_P: D_CAM0_ESD.3, J_CAM0_CAM1.4
CAM0_CSI_D1_N: D_CAM0_ESD.6, J_CAM0_CAM1.5
CAM0_CSI_D1_P: D_CAM0_ESD.5, J_CAM0_CAM1.6
CAM0_CSI_D2_N: D_CAM0_ESD.8, J_CAM0_CAM1.7
CAM0_CSI_D2_P: D_CAM0_ESD.7, J_CAM0_CAM1.8
CAM0_CSI_D3_N: D_CAM0_ESD.10, J_CAM0_CAM1.9
CAM0_CSI_D3_P: D_CAM0_ESD.9, J_CAM0_CAM1.10
CAM0_RESET_N: J_CAM0_CAM1.19, U_CAM_PWR.4
CAM1_CSI_CLK_N: D_CAM1_ESD.2, J_CAM0_CAM1.11
CAM1_CSI_CLK_P: D_CAM1_ESD.1, J_CAM0_CAM1.12
CAM1_CSI_D0_N: D_CAM1_ESD.4, J_CAM0_CAM1.13
CAM1_CSI_D0_P: D_CAM1_ESD.3, J_CAM0_CAM1.14
CAM1_CSI_D1_N: D_CAM1_ESD.6, J_CAM0_CAM1.15
CAM1_CSI_D1_P: D_CAM1_ESD.5, J_CAM0_CAM1.16
CAM1_RESET_N: J_CAM0_CAM1.20, U_CAM_PWR.5
CAM_AVDD_2V8: C_CAM_RAILS.1, J_CAM0_CAM1.21, TP_CAM_AVDD_2V8.1, U_CAM_PWR.1, U_PMIC_CHARGER.10
CAM_DVDD_1V2: C_CAM_RAILS.2, U_CAM_PWR.2, U_PMIC_CHARGER.11
CELL_GNSS_RF: MN_GNSS.1, MN_GNSS.2, MN_GNSS.3, RFTP_GNSS.1, U_GNSS_RF.1
CELL_RF_DIV: MN_CELL_DIV.1, MN_CELL_DIV.2, MN_CELL_DIV.3, RFTP_CELL_DIV.1
CELL_RF_MAIN: MN_CELL_MAIN.1, MN_CELL_MAIN.2, MN_CELL_MAIN.3, RFTP_CELL_MAIN.1
CHG_I2C_SCL: RN_PMIC_CTL.5, U_FG.3
CHG_I2C_SDA: RN_PMIC_CTL.6, U_FG.4
CODEC_INT: J_TOP_BOTTOM_FLEX_BOTTOM.20, J_TOP_BOTTOM_FLEX_TOP.20, RN_AUDIO_CTL.3, U_AUDIO_SPK_MIC.9
DISP_AVDD_5V5: C_DISP_RAILS.1, TP_DISP_AVDD_5V5.1, U_DISP_BIAS.1, U_PMIC_CHARGER.12
DISP_AVEE_N5V5: C_DISP_RAILS.2, U_DISP_BIAS.2, U_PMIC_CHARGER.13
DISP_BL_EN: J_DISPLAY_TOUCH.13, U_DISP_BIAS.3
DISP_BL_PWM: J_DISPLAY_TOUCH.14, U_DISP_BIAS.4
DISP_RESET_N: J_DISPLAY_TOUCH.11, U_DISP_BIAS.5
DSI_CLK_N: D_DSI_ESD.2, J_DISPLAY_TOUCH.2
DSI_CLK_P: D_DSI_ESD.1, J_DISPLAY_TOUCH.1
DSI_D0_N: D_DSI_ESD.4, J_DISPLAY_TOUCH.4
DSI_D0_P: D_DSI_ESD.3, J_DISPLAY_TOUCH.3
DSI_D1_N: D_DSI_ESD.6, J_DISPLAY_TOUCH.6
DSI_D1_P: D_DSI_ESD.5, J_DISPLAY_TOUCH.5
DSI_D2_N: D_DSI_ESD.8, J_DISPLAY_TOUCH.8
DSI_D2_P: D_DSI_ESD.7, J_DISPLAY_TOUCH.7
DSI_D3_N: D_DSI_ESD.10, J_DISPLAY_TOUCH.10
DSI_D3_P: D_DSI_ESD.9, J_DISPLAY_TOUCH.9
GND: C_AMP.3, C_AON.3, C_AP_RAILS.4, C_AUDIO.3, C_CAM_RAILS.4, C_DISP_RAILS.4, C_PMIC_IN.3, C_RF_RAILS.3, C_SOC_CORE.4, C_USBPD.2, D_CAM0_ESD.11, D_CAM1_ESD.7, D_CC_ESD.3, D_DSI_ESD.11, D_KEYS_ESD.4, D_MIC.4, D_SPK.3, D_TOUCH_ESD.5, D_USB2_ESD.3, D_USIM.6, D_VBUS_TVS.2, FL_CHG_IN.3, J_BATTERY.2, J_DEBUG.11, J_TOP_BOTTOM_FLEX_BOTTOM.25, J_TOP_BOTTOM_FLEX_BOTTOM.26, J_TOP_BOTTOM_FLEX_BOTTOM.27, J_TOP_BOTTOM_FLEX_BOTTOM.28, J_TOP_BOTTOM_FLEX_BOTTOM.29, J_TOP_BOTTOM_FLEX_BOTTOM.30, J_TOP_BOTTOM_FLEX_BOTTOM.31, J_TOP_BOTTOM_FLEX_BOTTOM.32, J_TOP_BOTTOM_FLEX_BOTTOM.33, J_TOP_BOTTOM_FLEX_BOTTOM.34, J_TOP_BOTTOM_FLEX_BOTTOM.35, J_TOP_BOTTOM_FLEX_BOTTOM.36, J_TOP_BOTTOM_FLEX_BOTTOM.37, J_TOP_BOTTOM_FLEX_BOTTOM.38, J_TOP_BOTTOM_FLEX_BOTTOM.39, J_TOP_BOTTOM_FLEX_BOTTOM.40, J_TOP_BOTTOM_FLEX_BOTTOM.41, J_TOP_BOTTOM_FLEX_BOTTOM.42, J_TOP_BOTTOM_FLEX_BOTTOM.43, J_TOP_BOTTOM_FLEX_BOTTOM.44, J_TOP_BOTTOM_FLEX_BOTTOM.45, J_TOP_BOTTOM_FLEX_BOTTOM.46, J_TOP_BOTTOM_FLEX_BOTTOM.47, J_TOP_BOTTOM_FLEX_BOTTOM.48, J_TOP_BOTTOM_FLEX_BOTTOM.49, J_TOP_BOTTOM_FLEX_TOP.25, J_TOP_BOTTOM_FLEX_TOP.26, J_TOP_BOTTOM_FLEX_TOP.27, J_TOP_BOTTOM_FLEX_TOP.28, J_TOP_BOTTOM_FLEX_TOP.29, J_TOP_BOTTOM_FLEX_TOP.30, J_TOP_BOTTOM_FLEX_TOP.31, J_TOP_BOTTOM_FLEX_TOP.32, J_TOP_BOTTOM_FLEX_TOP.33, J_TOP_BOTTOM_FLEX_TOP.34, J_TOP_BOTTOM_FLEX_TOP.35, J_TOP_BOTTOM_FLEX_TOP.36, J_TOP_BOTTOM_FLEX_TOP.37, J_TOP_BOTTOM_FLEX_TOP.38, J_TOP_BOTTOM_FLEX_TOP.39, J_TOP_BOTTOM_FLEX_TOP.40, J_TOP_BOTTOM_FLEX_TOP.41, J_TOP_BOTTOM_FLEX_TOP.42, J_TOP_BOTTOM_FLEX_TOP.43, J_TOP_BOTTOM_FLEX_TOP.44, J_TOP_BOTTOM_FLEX_TOP.45, J_TOP_BOTTOM_FLEX_TOP.46, J_TOP_BOTTOM_FLEX_TOP.47, J_TOP_BOTTOM_FLEX_TOP.48, J_TOP_BOTTOM_FLEX_TOP.49, MN_CELL_DIV.4, MN_CELL_DIV.5, MN_CELL_MAIN.4, MN_CELL_MAIN.5, MN_GNSS.4, MN_GNSS.5, MN_NFC.3, MN_WIFI0.4, MN_WIFI0.5, MN_WIFI1.4, MN_WIFI1.5, RC_1.3, RC_2.3, RC_3.3, RN_AUDIO_CTL.6, RN_AUDIO_DIG.7, RN_BAT_SENSE.4, RN_CAM_I2C.8, RN_LPDDR_CA.7, RN_LPDDR_DIFF.5, RN_LPDDR_DQ.5, RN_PMIC_CTL.13, RN_UFS.8, RS_PWR.5, SW_POWER_VOL.5, U_CAM_PWR.7, U_DISP_BIAS.7, U_ESIM.6, U_FG.7, U_GNSS_RF.4, U_HAPTIC.4, U_NFC.8, U_PMIC_CHARGER.9, U_SENS.9, U_SOC_LPDDR_UFS.18
HAPTIC_OUT: J_TOP_BOTTOM_FLEX_BOTTOM.22, J_TOP_BOTTOM_FLEX_TOP.22, U_AUDIO_SPK_MIC.13, U_HAPTIC.1
I2S_BCLK: J_TOP_BOTTOM_FLEX_BOTTOM.12, J_TOP_BOTTOM_FLEX_TOP.12, RN_AUDIO_DIG.1, U_AUDIO_SPK_MIC.1
I2S_DIN: J_TOP_BOTTOM_FLEX_BOTTOM.15, J_TOP_BOTTOM_FLEX_TOP.15, RN_AUDIO_DIG.4, U_AUDIO_SPK_MIC.4
I2S_DOUT: J_TOP_BOTTOM_FLEX_BOTTOM.14, J_TOP_BOTTOM_FLEX_TOP.14, RN_AUDIO_DIG.3, U_AUDIO_SPK_MIC.3
I2S_LRCLK: J_TOP_BOTTOM_FLEX_BOTTOM.13, J_TOP_BOTTOM_FLEX_TOP.13, RN_AUDIO_DIG.2, U_AUDIO_SPK_MIC.2
IO_1V8: C_AP_RAILS.3, C_AUDIO.2, C_CAM_RAILS.3, C_DISP_RAILS.3, C_RF_RAILS.2, C_SOC_CORE.3, J_CAM0_CAM1.22, J_DEBUG.10, J_TOP_BOTTOM_FLEX_BOTTOM.9, J_TOP_BOTTOM_FLEX_TOP.9, RN_AUDIO_CTL.5, RN_CAM_I2C.7, TP_IO_1V8.1, U_CAM_PWR.3, U_CELL.2, U_DISP_BIAS.6, U_ESIM.5, U_GNSS_RF.3, U_HAPTIC.3, U_NFC.7, U_PMIC_CHARGER.7, U_SENS.8, U_SOC_LPDDR_UFS.17, U_WIFI_BT.19
LPDDR_CA0: RN_LPDDR_CA.1, U_SOC_LPDDR_UFS.1
LPDDR_CA1: RN_LPDDR_CA.2, U_SOC_LPDDR_UFS.2
LPDDR_CA2: RN_LPDDR_CA.3, U_SOC_LPDDR_UFS.3
LPDDR_CA3: RN_LPDDR_CA.4, U_SOC_LPDDR_UFS.4
LPDDR_CK_N: RN_LPDDR_DIFF.2, U_SOC_LPDDR_UFS.5
LPDDR_CK_P: RN_LPDDR_DIFF.1, U_SOC_LPDDR_UFS.6
LPDDR_DQ0: RN_LPDDR_DQ.1, U_SOC_LPDDR_UFS.7
LPDDR_DQ1: RN_LPDDR_DQ.2, U_SOC_LPDDR_UFS.8
LPDDR_DQ2: RN_LPDDR_DQ.3, U_SOC_LPDDR_UFS.9
LPDDR_DQ3: RN_LPDDR_DQ.4, U_SOC_LPDDR_UFS.10
LPDDR_DQS_N: RN_LPDDR_DIFF.4, U_SOC_LPDDR_UFS.11
LPDDR_DQS_P: RN_LPDDR_DIFF.3, U_SOC_LPDDR_UFS.12
LPDDR_RESET_N: RN_LPDDR_CA.5, U_SOC_LPDDR_UFS.13
LPDDR_ZQ: RN_LPDDR_CA.6, U_SOC_LPDDR_UFS.14
NFC_RF_N: MN_NFC.2, U_NFC.6
NFC_RF_P: MN_NFC.1, U_NFC.5
PDM_CLK: D_MIC.1, J_TOP_BOTTOM_FLEX_BOTTOM.16, J_TOP_BOTTOM_FLEX_TOP.16, RN_AUDIO_DIG.5, U_AUDIO_SPK_MIC.5
PDM_DAT: D_MIC.2, J_TOP_BOTTOM_FLEX_BOTTOM.17, J_TOP_BOTTOM_FLEX_TOP.17, RN_AUDIO_DIG.6, U_AUDIO_SPK_MIC.6
PWR_KEY_N: C_AON.2, D_KEYS_ESD.1, RC_1.1, SW_POWER_VOL.1
RF_VBAT: C_RF_RAILS.1, J_TOP_BOTTOM_FLEX_BOTTOM.24, J_TOP_BOTTOM_FLEX_TOP.24, RS_PWR.4, TP_RF_VBAT.1, U_CELL.1, U_GNSS_RF.2, U_PMIC_CHARGER.8
SHIELD_GND: J_TOP_BOTTOM_FLEX_BOTTOM.6, J_TOP_BOTTOM_FLEX_TOP.6, J_USB_C.6
SPK_N: D_SPK.2, U_AUDIO_SPK_MIC.12
SPK_P: D_SPK.1, U_AUDIO_SPK_MIC.11
SYS: C_AMP.2, C_PMIC_IN.1, FL_CHG_IN.2, J_TOP_BOTTOM_FLEX_BOTTOM.7, J_TOP_BOTTOM_FLEX_TOP.7, RS_PWR.3, TP_SYS.1, U_FG.2, U_HAPTIC.2, U_PMIC_CHARGER.2
TOUCH_I2C_SCL: D_TOUCH_ESD.1, J_DISPLAY_TOUCH.15
TOUCH_I2C_SDA: D_TOUCH_ESD.2, J_DISPLAY_TOUCH.16
UFS_REFCLK_N: RN_UFS.2, U_SOC_LPDDR_UFS.19
UFS_REFCLK_P: RN_UFS.1, U_SOC_LPDDR_UFS.20
UFS_RESET_N: RN_UFS.7, U_SOC_LPDDR_UFS.21
UFS_RX_N: RN_UFS.6, U_SOC_LPDDR_UFS.22
UFS_RX_P: RN_UFS.5, U_SOC_LPDDR_UFS.23
UFS_TX_N: RN_UFS.4, U_SOC_LPDDR_UFS.24
USB_CC1: D_CC_ESD.1, J_TOP_BOTTOM_FLEX_BOTTOM.3, J_TOP_BOTTOM_FLEX_TOP.3, J_USB_C.4, USBTP_CC1.1
USB_CC2: D_CC_ESD.2, J_TOP_BOTTOM_FLEX_BOTTOM.4, J_TOP_BOTTOM_FLEX_TOP.4, J_USB_C.5, USBTP_CC2.1
USB_DN: D_USB2_ESD.2, J_TOP_BOTTOM_FLEX_BOTTOM.2, J_TOP_BOTTOM_FLEX_TOP.2, J_USB_C.3, USBTP_DN.1
USB_DP: D_USB2_ESD.1, J_TOP_BOTTOM_FLEX_BOTTOM.1, J_TOP_BOTTOM_FLEX_TOP.1, J_USB_C.2, USBTP_DP.1
USIM_CLK: D_USIM.2, U_CELL.9
USIM_IO: D_USIM.4, U_CELL.11
USIM_RST: D_USIM.3, U_CELL.10
VBAT: C_PMIC_IN.2, J_BATTERY.1, J_TOP_BOTTOM_FLEX_BOTTOM.23, J_TOP_BOTTOM_FLEX_TOP.23, RN_BAT_SENSE.1, RS_PWR.2, TP_VBAT.1, U_FG.1, U_PMIC_CHARGER.3
VBUS: D_VBUS_TVS.1, FL_CHG_IN.1, J_TOP_BOTTOM_FLEX_BOTTOM.5, J_TOP_BOTTOM_FLEX_TOP.5, J_USB_C.1, RS_PWR.1, TP_VBUS.1, USBTP_VBUS.1, U_PMIC_CHARGER.1
VDD_AMP_3V3: C_AMP.1, J_TOP_BOTTOM_FLEX_BOTTOM.11, J_TOP_BOTTOM_FLEX_TOP.11, U_AUDIO_SPK_MIC.16
VDD_AUDIO_3V3: C_AUDIO.1, D_MIC.3, J_TOP_BOTTOM_FLEX_BOTTOM.10, J_TOP_BOTTOM_FLEX_TOP.10, U_AUDIO_SPK_MIC.15
VOL_DOWN_N: D_KEYS_ESD.3, RC_3.1, SW_POWER_VOL.3
VOL_UP_N: D_KEYS_ESD.2, RC_2.1, SW_POWER_VOL.2
WIFI_BT_RF0: MN_WIFI0.1, MN_WIFI0.2, MN_WIFI0.3, RFTP_WIFI0.1
WIFI_BT_RF1: MN_WIFI1.1, MN_WIFI1.2, MN_WIFI1.3, RFTP_WIFI1.1
